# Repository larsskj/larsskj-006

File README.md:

An Arduino shield for larsskj-003 boards
========================================

### larsskj-006

This is an Arduino shield that can be used to control my larsskj-003 boards. It includes a TLC 5940 LED driver that is compatible with the standard Arduino library. This board compliments my larsskj-005 board: While the other board can be used for a quick LED test without programming, this board requires programming, but enables proper settings of light power.

The shield is powered by a 7805 regulator and should be connected to a DC power supply of 9-30 volt. The shield works as a power supply for the attached Arduino as well.

For more information, visit the [project homepage](https://larsskj.org/projects/larsskj-006).

The files provided are project files for [KiCad 5](http://kicad-pcb.org/).

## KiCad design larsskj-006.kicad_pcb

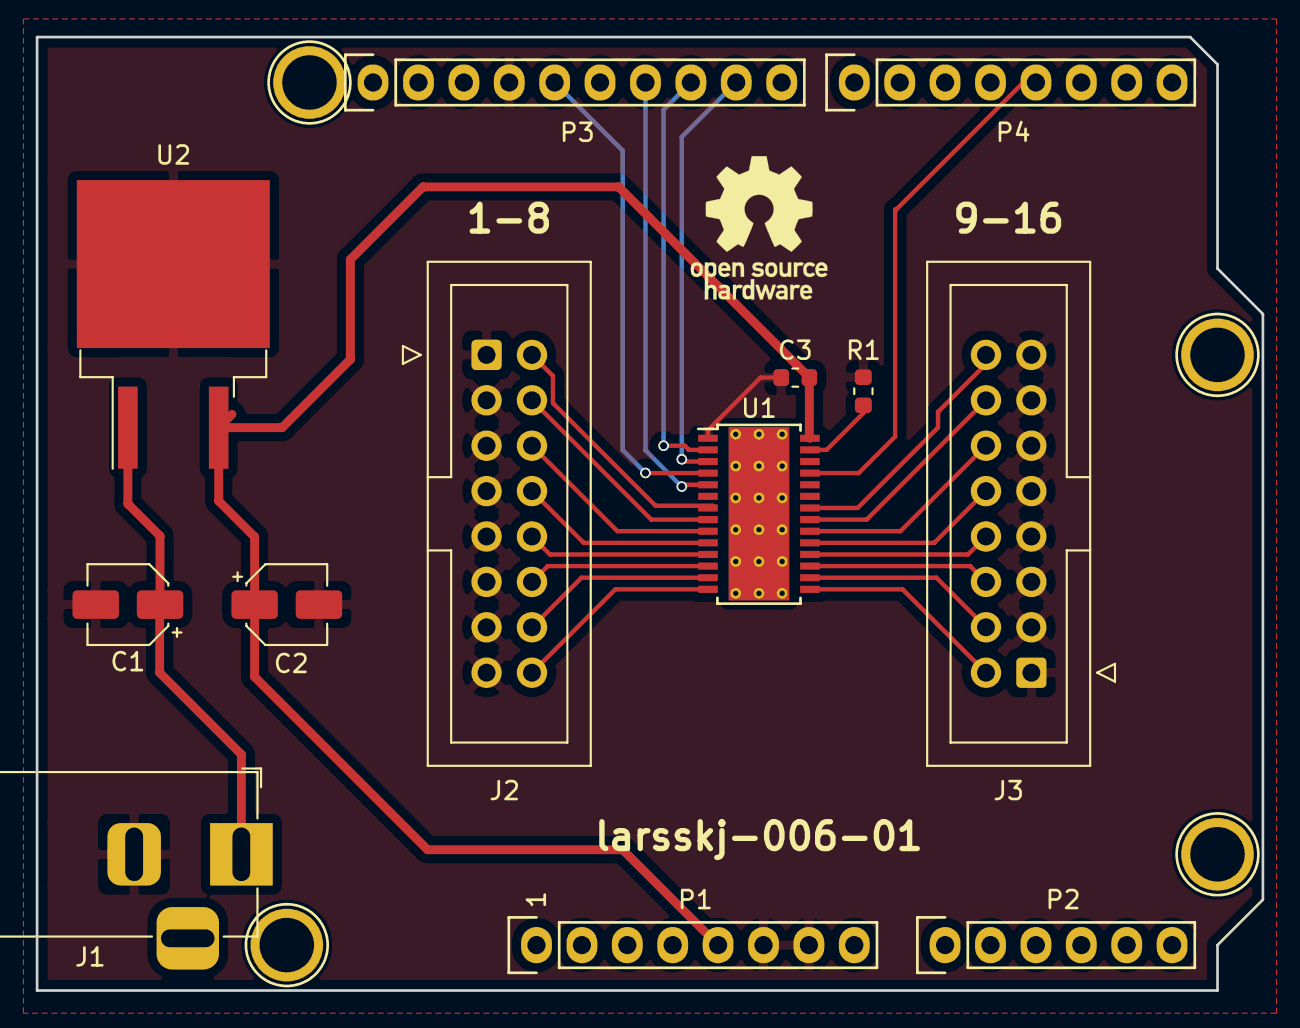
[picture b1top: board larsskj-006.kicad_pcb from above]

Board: 2 copper layers, 68.6 x 53.3 mm, 17 parts (0 on the bottom side), 25 nets.

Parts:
C1, C2: 10uF; CP_Elec_4x5.3
C3: 0.1uF; R_0603_1608Metric
J1: Barrel_Jack; BarrelJack_Horizontal
J2, J3: IDC 16 pin; IDC-Header_2x08_P2.54mm_Vertical
P1: Power; Socket_Strip_Arduino_1x08
P2: Analog; Socket_Strip_Arduino_1x06
P3: Digital; Socket_Strip_Arduino_1x10
P4: Digital; Socket_Strip_Arduino_1x08
P5, P6, P7, P8: CONN_01X01; Arduino_1pin
R1: 2.2K; R_0603_1608Metric
U1: TLC5940; HTSSOP-28-1EP_4.4x9.7mm_P0.65mm_EP3.4x9.5mm_Mask2.4x6.17mm_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
U2: LM7805; TO-263-2

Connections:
GND: C1.2, C2.2, C3.2, J1.2, J2.1, J2.3, J2.5, J2.7, J2.9, J2.11, J2.13, J2.15, J3.1, J3.3, J3.5, J3.7, J3.9, J3.11, J3.13, J3.15, P1.6, P1.7, P3.4, R1.2, U1.1, U2.2
unnamed: C1.1, J1.1, U2.1
unnamed: J2.2, U1.7
unnamed: J2.4, U1.8
unnamed: J2.6, U1.9
unnamed: J2.8, U1.10
unnamed: J2.10, U1.11
unnamed: J2.12, U1.12
unnamed: J2.14, U1.13
unnamed: J2.16, U1.14
unnamed: J3.2, U1.15
unnamed: J3.4, U1.16
unnamed: J3.6, U1.17
unnamed: J3.8, U1.18
unnamed: J3.10, U1.19
unnamed: J3.12, U1.20
unnamed: J3.14, U1.21
unnamed: J3.16, U1.22
unnamed: P3.5, U1.4
unnamed: P3.7, U1.5
unnamed: P3.8, U1.2
unnamed: P3.9, U1.3
unnamed: P4.5, U1.25
unnamed: R1.1, U1.27
VCC: C2.1, C3.1, P1.5, U1.28, U2.3

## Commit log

2020-09-19 README added
2020-09-19 README updated
2020-09-19 Part numbers added
